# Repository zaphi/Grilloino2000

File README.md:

# Grilloino2000

ESP8266 Grillthermometer

Als leidenschaftlicher Griller war es dies Jahr zeit für einen Smoker! Da kaufen nicht in frage kommt wurde der Bau eines UDS geplant. Und da ich in der Nacht gerne Schlafe und nicht alle halbe Stunde zum Smoker laufen möchte, musste man hier automatisieren.

Bauteile:
- ESP8266 NodeMCU
- 4051N Analogmultiplexer
- 16x2 LCD
- kleinkram... siehe BOM.txt

Funktionen:
- 1x Garraum
- 1-3x Kerntemperatur
- WIFI
- Handy App mittels Blynk
- Thingspeak Logging
- Pitmaster (Lüfter/Klappe)
- Push Nachrichten
- HTTP Server (wird vermutlich entfernt)

Aktueller Projektstand:
- PCB V3.1 incl. Buttons 
- 3D Druck Gehäuse

ToDo:
- korrektur Polung DC Stecker in PCB V3.2

HowTo:
- Es können theoretisch  alle Fühler verwendet werden die auch beim [WLANThermo V2](https://github.com/WLANThermo/WLANThermo_v2/tree/master/software/usr/share/doc/WLANThermo/probedata) funktionieren. Dort wird auch mittels der Steinhart-Hart-Gleichung gerechnet somit können die Parameter A,B,C und Rn übernommen werden. Danke für das vermessen der  Sensoren :-)

Aktuell eingepflegt:
- Maverick ET-7/71/72/73/77/901b
- Maverick ET-735
- Maverick ET-732/733
- Ikkea Fantast
- Ikkea Fantast Neu

Einstellungen für Blynk:
- char auth[] = "PUT YOUR CODE HEAR";

Einstellungen Thingspeak
- const int channelID = Your ID;
- String writeAPIKey = "Your Key";

Messen und Korrektur V3.3:
- Spannung an JP1 messen und im Code eintragen z.B. 3.293V
- float vin = 3.293;  

Button S1:
- Startet WiFi Konfigurations Mode. Grilloino wird als AP im Handy sichtbar und kann mit jedem beliebigen
Hotspot verubnden werden.

Button S2:
- Doppelklick -> Menü Seite -
- Einfach Klick -> Wert +1
- Langer Klick -> Wert ++

Button S3:
- Doppelklick -> Menü Seite +
- Einfach Klick -> Wert -1
- Langer Klick -> Wert --
- Langer Klick nicht im Menü -> anzeige Spannung, IP und RSSI

Bauteile:
- R1-R4 47kOhm Messwiderstand
- R5 560 Ohm
- R9,R10,R11,R13,R14 10kOhm
- R12 47 kOhm

- C1 0,33uf
- C2 0,1uf
- C3,C4,C5,C6 1000 uf
- IC2 LM7805
- Q1 STP36NF06L
- IC1 4051N

Benötigte libraries:

- [Wifi Manager](https://github.com/tzapu/WiFiManager)
- [OneButton](https://github.com/mathertel/OneButton)
- [Timer](https://github.com/JChristensen/Timer)
- [LiquidCrystal-I2C-library](https://github.com/fdebrabander/Arduino-LiquidCrystal-I2C-library)
- [Blynk](https://github.com/blynkkk/blynk-library/releases/tag/v0.5.4)
- [PID-Library](https://github.com/br3ttb/Arduino-PID-Library)

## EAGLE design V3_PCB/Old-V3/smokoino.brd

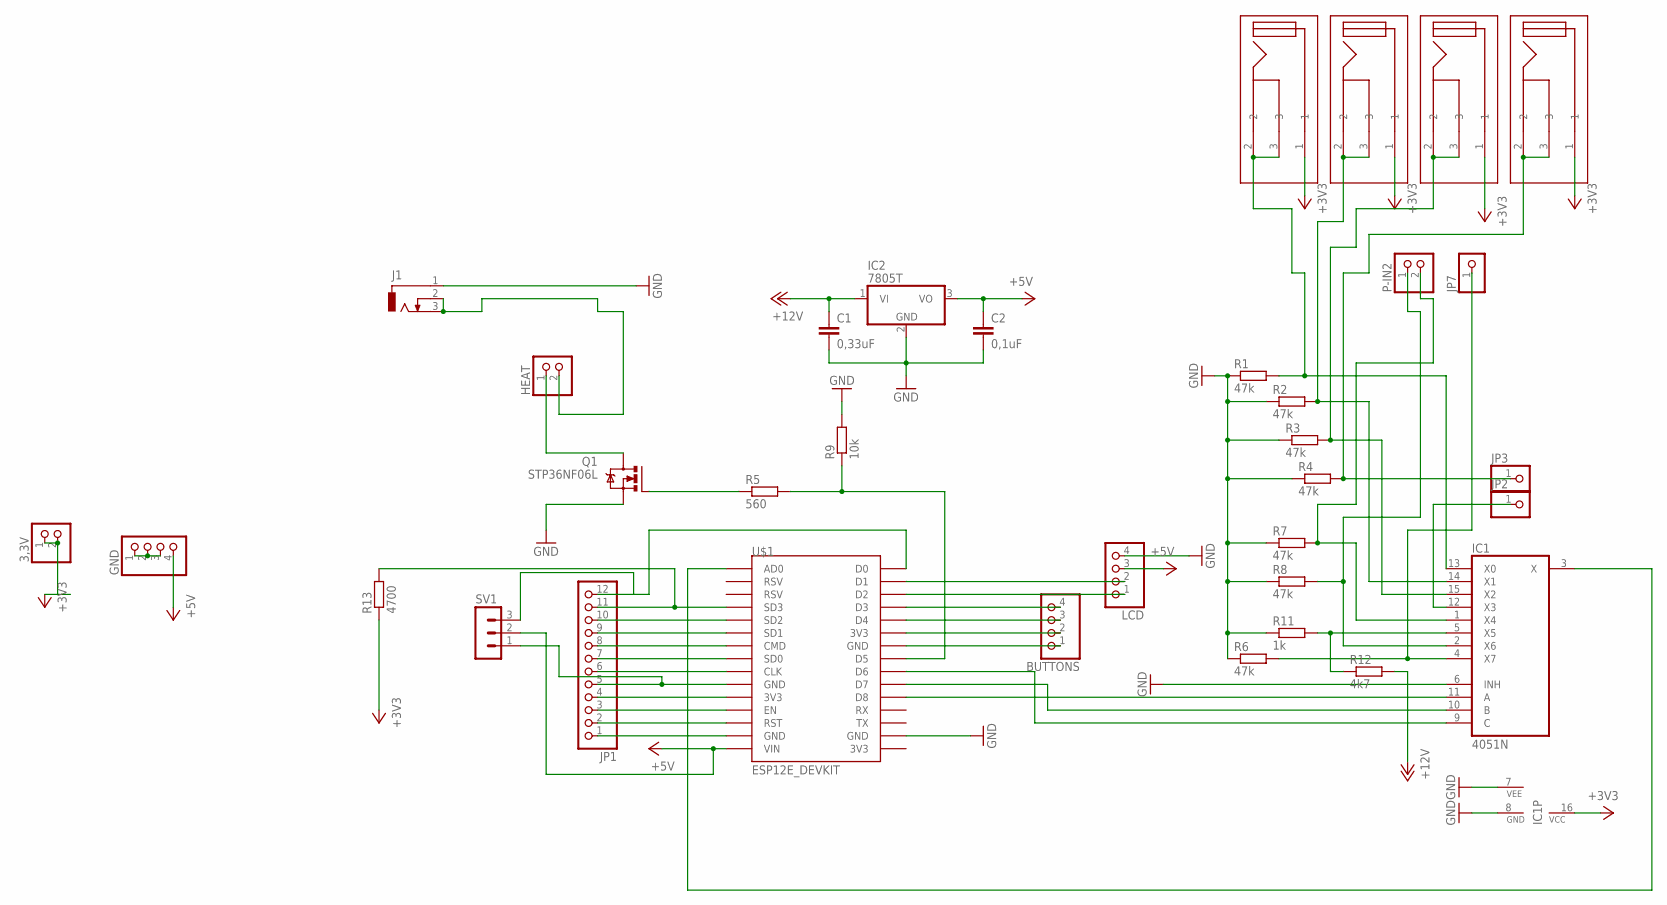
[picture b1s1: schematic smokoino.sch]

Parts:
3,3V: PINHD-1X2; 1X02
BUTTONS: PINHD-1X4; 1X04
C1: 0,33uF; C5B2.5
C2: 0,1uF; C5B2.5
GND: PINHD-1X4; 1X04
HEAT: PINHD-1X2; 1X02
IC1: 4051N; DIL16
IC2: 7805T; TO220H
J1: DCJ0303
JP1: PINHD-1X12; 1X12
JP2, JP3, JP7: PINHD-1X1; 1X01
LCD: PINHD-1X4; 1X04
P-IN2: PINHD-1X2; 1X02
Q1: STP36NF06L; TO220BV
R1, R2, R3, R4, R6, R7, R8: 47k; 0207/10
R5: 560; 0207/10
R9: 10k; 0207/10
R11: 1k; 0207/10
R12: 4k7; 0207/10
R13: 4700; 0207/10
SV1: MA03-1
U$1: ESP12E_DEVKIT
U$3, U$4, U$5, U$6: JACK_2_5

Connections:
4051: IC1.4 (X7), JP7.1, R6.2
+3V3: 3,3V.1, 3,3V.2, IC1.16 (VCC), JP1.4, R13.1, U$1.3V3@0 (3V3), U$3.1, U$4.1, U$5.1, U$6.1
+5V: C2.1, GND.4, IC2.3 (VO), LCD.3, SV1.2, U$1.VIN
+12V: C1.1, HEAT.2, IC2.1 (VI), J1.2, J1.3, R12.2
GND: BUTTONS.1, C1.2, C2.2, GND.1, GND.2, GND.3, IC1.6 (INH), IC1.7 (VEE), IC1.8 (GND), IC2.2 (GND), J1.1, JP1.1, JP1.5, LCD.4, Q1.S, R1.1, R2.1, R3.1, R4.1, R6.1, R7.1, R8.1, R9.2, R11.1, SV1.1, U$1.GND@0 (GND), U$1.GND@1 (GND), U$1.GND@2 (GND), U$1.GND@3 (GND)
unnamed: IC1.9 (C), U$1.D6
unnamed: IC1.10 (B), U$1.D7
unnamed: IC1.11 (A), U$1.D8
unnamed: IC1.3 (X), U$1.AD0
unnamed: IC1.13 (X0), R1.2, U$3.2, U$3.3
unnamed: IC1.14 (X1), R2.2, U$4.2, U$4.3
unnamed: BUTTONS.4, U$1.D3
unnamed: BUTTONS.3, U$1.D4
unnamed: LCD.1, U$1.D2
unnamed: LCD.2, U$1.D1
unnamed: IC1.15 (X2), R3.2, U$5.2, U$5.3
unnamed: IC1.5 (X5), R11.2, R12.1
unnamed: JP1.10, U$1.SD2
unnamed: IC1.12 (X3), JP2.1
unnamed: IC1.2 (X6), P-IN2.1, R8.2
unnamed: R5.2, R9.1, U$1.D5
unnamed: JP1.2, U$1.RST
unnamed: JP1.3, U$1.EN
unnamed: BUTTONS.2, U$1.3V3@1 (3V3)
unnamed: JP1.6, U$1.CLK
unnamed: JP1.7, U$1.SD0
unnamed: JP1.8, U$1.CMD
unnamed: JP1.9, U$1.SD1
unnamed: Q1.G, R5.1
unnamed: JP1.11, R13.2, U$1.SD3
unnamed: JP1.12, SV1.3, U$1.D0
unnamed: IC1.1 (X4), P-IN2.2, R7.2
unnamed: JP3.1, R4.2, U$6.2, U$6.3
STP36NF06L: HEAT.1, Q1.D

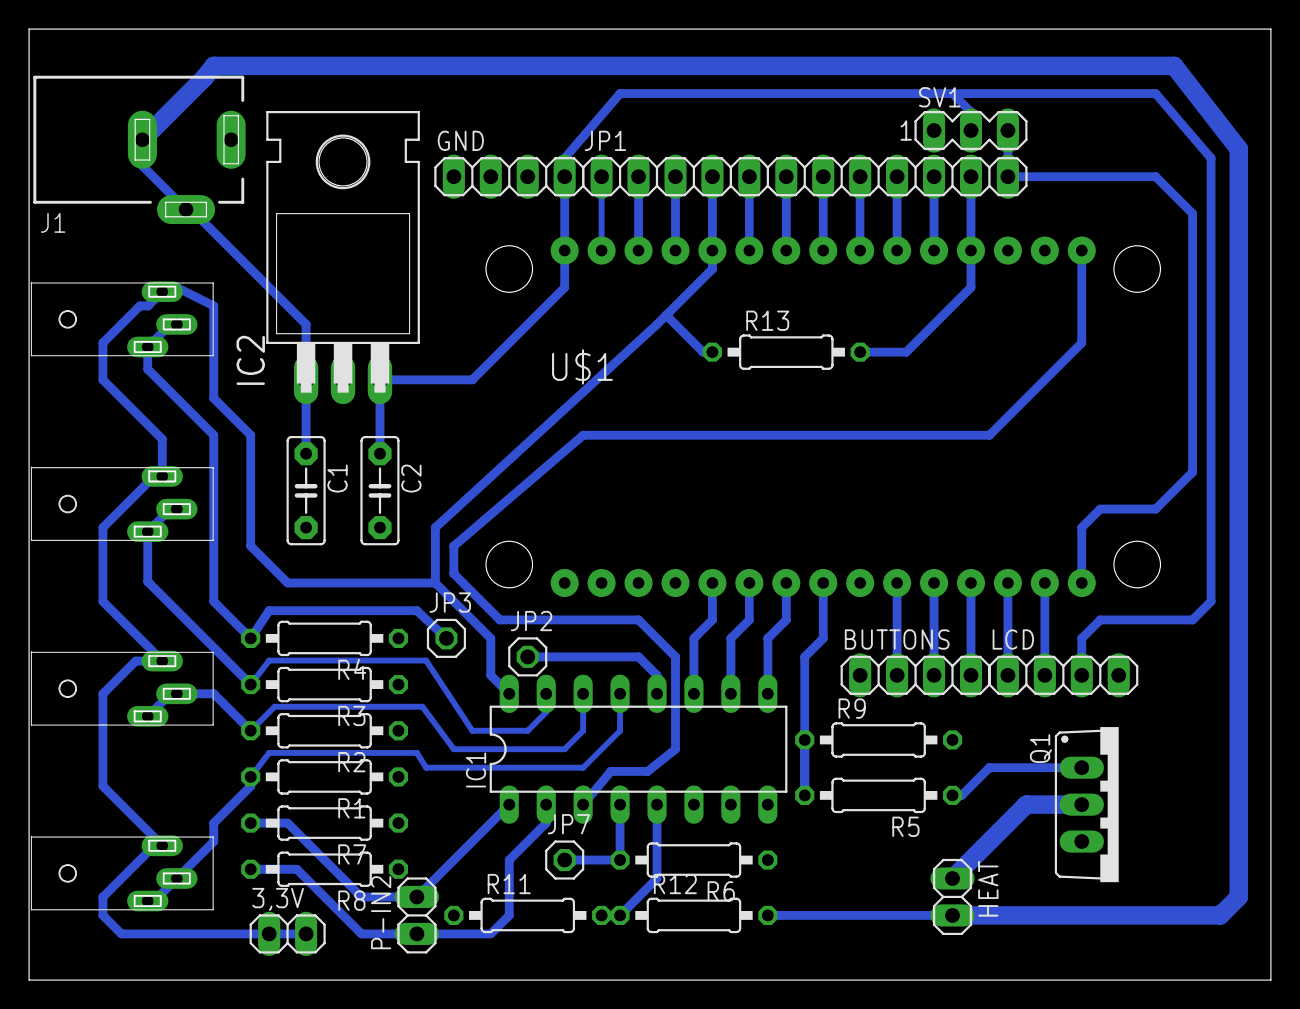
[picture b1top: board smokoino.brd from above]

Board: 2 copper layers, 85.3 x 65.3 mm, 34 parts (0 on the bottom side), 34 nets.

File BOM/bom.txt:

Partlist

Exported from smokoino.sch at 05.09.2018 19:11

EAGLE Version 7.5.0 Copyright (c) 1988-2015 CadSoft

Assembly variant: 

Part     Value          Device        Package       Library          Sheet

3,3V                    PINHD-1X2     1X02          pinhead          1
BUTTONS                 PINHD-1X4     1X04          pinhead          1
C1       0,33uF         C5/2.5        C5B2.5        capacitor-wima   1
C2       0,1uF          C5/2.5        C5B2.5        capacitor-wima   1
GND                     PINHD-1X4     1X04          pinhead          1
HEAT                    PINHD-1X2     1X02          pinhead          1
IC1      4051N          4051N         DIL16         40xx             1
IC2      7805T          7805T         TO220H        linear           1
J1                      DCJ0303       DCJ0303       con-jack         1
JP1                     PINHD-1X12    1X12          pinhead          1
JP2                     PINHD-1X1     1X01          pinhead          1
JP3                     PINHD-1X1     1X01          pinhead          1
JP7                     PINHD-1X1     1X01          pinhead          1
LCD                     PINHD-1X4     1X04          pinhead          1
P-IN2                   PINHD-1X2     1X02          pinhead          1
Q1       STP36NF06L     IRF540        TO220BV       transistor-power 1
R1       47k            R-EU_0207/10  0207/10       rcl              1
R2       47k            R-EU_0207/10  0207/10       rcl              1
R3       47k            R-EU_0207/10  0207/10       rcl              1
R4       47k            R-EU_0207/10  0207/10       rcl              1
R5       560            R-EU_0207/10  0207/10       rcl              1
R6       47k            R-EU_0207/10  0207/10       rcl              1
R7       47k            R-EU_0207/10  0207/10       rcl              1
R8       47k            R-EU_0207/10  0207/10       rcl              1
R9       10k            R-EU_0207/10  0207/10       rcl              1
R11      1k             R-EU_0207/10  0207/10       rcl              1
R12      4k7            R-EU_0207/10  0207/10       rcl              1
R13      4700           R-EU_0207/10  0207/10       rcl              1
SV1                     MA03-1        MA03-1        con-lstb         1
U$1      ESP12E_DEVKIT  ESP12E_DEVKIT ESP12E_DEVKIT ESP12E_DEVKIT    1
U$3      JACK_2_5       JACK_2_5      JACK_2_5      2_5mm_jack       1
U$4      JACK_2_5       JACK_2_5      JACK_2_5      2_5mm_jack       1
U$5      JACK_2_5       JACK_2_5      JACK_2_5      2_5mm_jack       1
U$6      JACK_2_5       JACK_2_5      JACK_2_5      2_5mm_jack       1

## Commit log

2018-09-07 Bilder Schaltplan Layout
2018-09-07 Teileliste erstellt
2018-09-07 option Display
2018-09-07 code cleanup and more blynk functions
2018-09-07 upadte blynk app
2018-09-07 update app
2018-09-14 update push and servo speed
    removed Pushingbox.
    Push is done with blynk
    changed servo speed to save power and cool down the litle lm7805
2018-09-18 probe.h included
2018-09-23 Big Update V3.1
2018-09-23 v3.1
2018-09-23 upadate
2018-09-24 New NodeMCU AZDelivery is crap!!
2018-09-25 Diode added
2018-09-25 3d-Print update
2018-09-29 update Gerber V3.2
    DC-Plug Positiv Polarity
2018-09-29 3-D Druck klappe
2018-09-30 upate
2018-10-05 libaries added
2019-05-06 fixed wrong value for Servo
